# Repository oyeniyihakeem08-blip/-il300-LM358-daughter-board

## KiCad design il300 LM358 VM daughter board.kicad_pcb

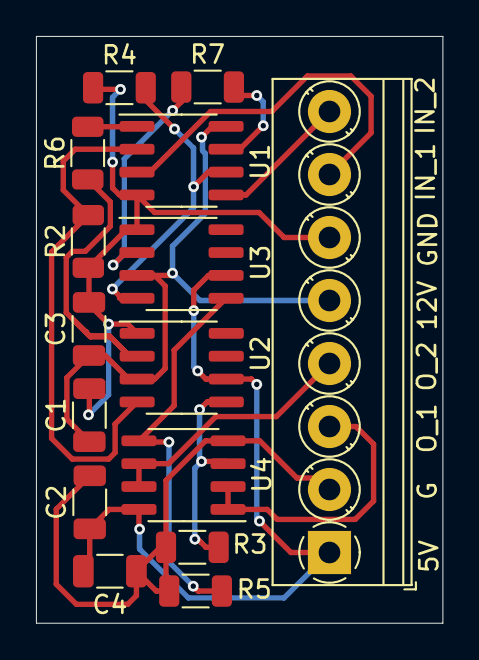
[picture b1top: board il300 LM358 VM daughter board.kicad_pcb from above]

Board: 2 copper layers, 22.6 x 32.6 mm, 15 parts (0 on the bottom side), 16 nets.

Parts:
C1, C2, C3, C4: 0.1; C_1206_3216Metric
J1: Screw_Terminal_01x08; TerminalBlock_Phoenix_PT-1,5-8-3.5-H_1x08_P3.50mm_Horizontal
R2, R3, R4, R5: 18k; R_1206_3216Metric
R6, R7: 100R; R_1206_3216Metric
U1, U4: LM358; SOIC-8_3.9x4.9mm_P1.27mm
U2, U3: IL300; SOIC-8_3.9x4.9mm_P1.27mm

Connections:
/5V(MCU): C2.1, C4.2, J1.1, U2.6, U3.6, U4.8 (V+)
/12V_IN: C1.1, C3.1, J1.5, U1.8 (V+), U2.3, U3.3
/SIG_IN_1: J1.7, U1.3 (+)
/SIG_IN_2: J1.8, U1.5 (+)
/SIG_OUT_1: J1.3, U4.1, U4.2 (-)
/SIG_OUT_2: J1.4, U4.6 (-), U4.7
GND: C1.2, C3.2, J1.6, R2.1, R4.1, U1.4 (V-), U2.1, U3.1
GNDREF: C2.2, C4.1, J1.2, R3.1, R5.1, U4.4 (V-)
unnamed: R6.1, U2.2
unnamed: R6.2, U1.1
unnamed: R7.1, U3.2
unnamed: R7.2, U1.7
unnamed: R2.2, U1.2 (-), U2.4
unnamed: R4.2, U1.6 (-), U3.4
unnamed: R3.2, U2.5, U4.3 (+)
unnamed: R5.2, U3.5, U4.5 (+)

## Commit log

2026-01-09 Schematics upload
2026-01-11 Update schematics
2026-01-13 Added schematics
